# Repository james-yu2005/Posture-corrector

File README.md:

# 🎯 Posture Corrector Device

## 🎥 Demo Videos

Explore both iterations in action:

- ▶️ **ESP32 + OpenCV-based Posture Corrector (2nd Iteration)**  
- ▶️ **Arduino-based Posture Corrector (1st Iteration)**

📁 [Watch the Demo Videos on Google Drive](https://drive.google.com/drive/folders/1XhhxoisGqGbtTAvJfZo68UkWgdPwPm_9?usp=drive_link)

---

## 🧠 Overview

A wearable device that uses real-time sensor feedback and computer vision to promote proper posture.

This device monitors upper back and neck posture using an **MPU-6050** sensor and a custom **OpenCV** model. Upon detecting poor posture, it emits an audible alert via a buzzer to notify the user.

---

## 🔧 First Iteration (Prototype)

- Built using an **Arduino Uno R3**, **MPU-6050**, and a **breadboard**.
- Detected angular deviations in back posture and triggered a buzzer during slouching.

---

## 🚀 Second Iteration (Refined)

- Upgraded to an **ESP32** microcontroller for wireless communication and improved performance.
- Integrated an **OpenCV + MediaPipe** model to track **neck posture** using webcam input and calculate head tilt angles.
- Real-time communication between OpenCV and ESP32 triggers the buzzer when poor neck posture is detected.
- Designed a **3D-printed wearable enclosure** using **SolidWorks** to house the electronics.
- 📂 Computer vision source code: [OpenCV Posture Model](https://github.com/james-yu2005/posture_corrector_code)

---

## 🛠️ Hardware Improvements

- Designed a **custom PCB** to replace the breadboard, enhancing compactness, reliability, and ease of assembly.
- A new **SolidWorks 3D enclosure** is in development for the updated hardware version.

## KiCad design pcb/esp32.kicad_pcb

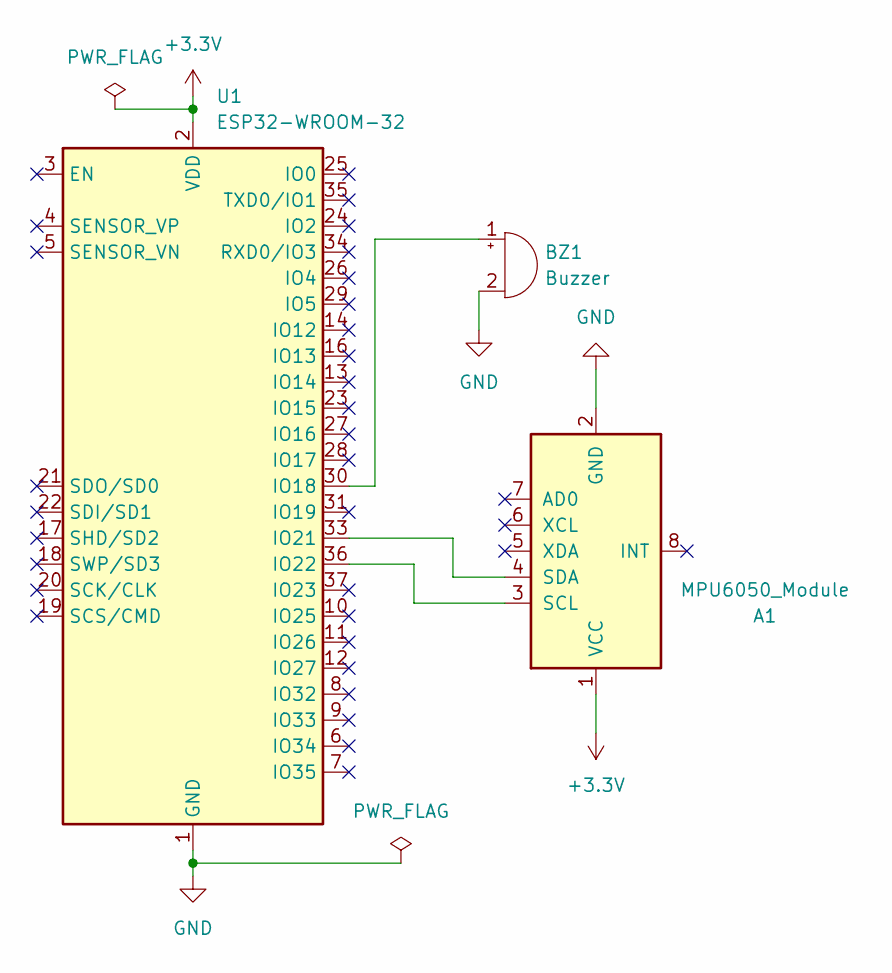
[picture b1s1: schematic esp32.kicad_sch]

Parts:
A1: MPU6050_Module
BZ1: Buzzer; Buzzer_12x9.5RM7.6
U1: ESP32-WROOM-32

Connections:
+3.3V: A1.1 (VCC), U1.2 (VDD)
GND: A1.2 (GND), BZ1.2 (-), U1.1 (GND), U1.15 (GND), U1.38 (GND), U1.39 (GND)
unnamed: A1.3 (SCL), U1.36 (IO22)
unnamed: A1.4 (SDA), U1.33 (IO21)
unnamed: BZ1.1 (+), U1.30 (IO18)

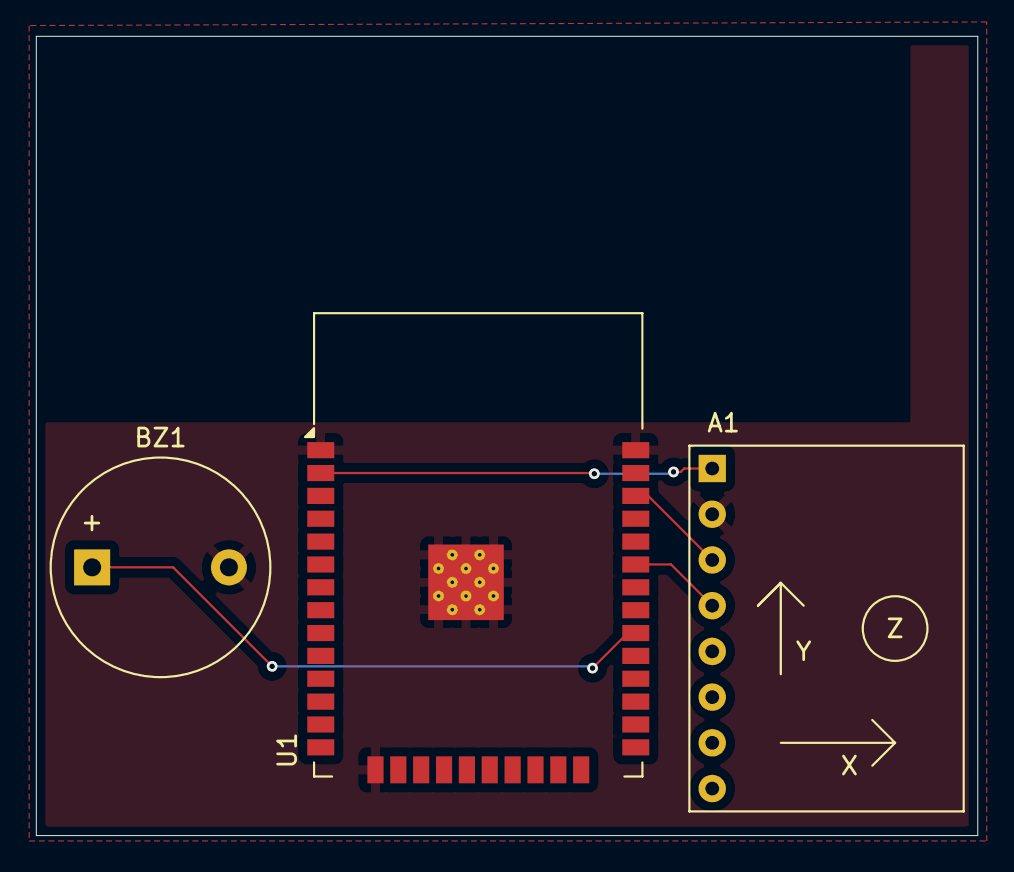
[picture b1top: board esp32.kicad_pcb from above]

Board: 4 copper layers, 52.3 x 44.4 mm, 3 parts (0 on the bottom side), 5 nets.

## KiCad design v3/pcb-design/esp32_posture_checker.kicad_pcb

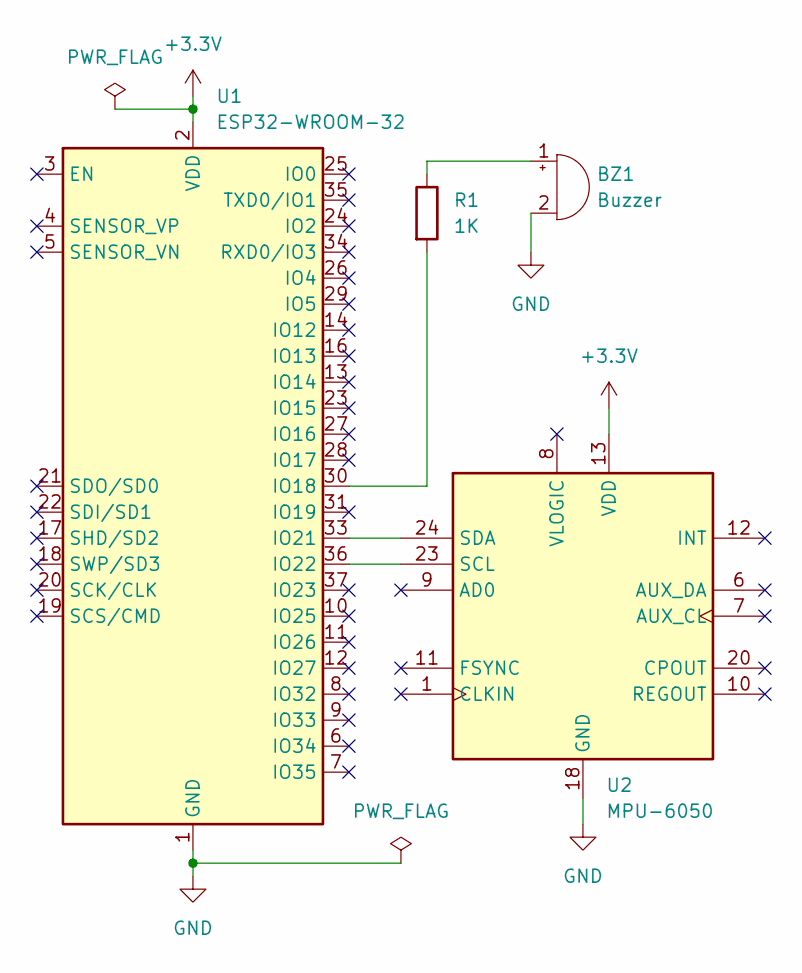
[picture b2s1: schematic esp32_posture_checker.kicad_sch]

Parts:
BZ1: Buzzer; Buzzer_12x9.5RM7.6
R1: 1K; R_Axial_DIN0207_L6.3mm_D2.5mm_P7.62mm_Horizontal
U1: ESP32-WROOM-32
U2: MPU-6050; InvenSense_QFN-24_4x4mm_P0.5mm

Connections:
+3.3V: U1.2 (VDD), U2.13 (VDD)
GND: BZ1.2 (-), U1.1 (GND), U1.15 (GND), U1.38 (GND), U1.39 (GND), U2.18 (GND)
unnamed: BZ1.1 (+), R1.1
unnamed: R1.2, U1.30 (IO18)
unnamed: U1.33 (IO21), U2.24 (SDA)
unnamed: U1.36 (IO22), U2.23 (SCL)

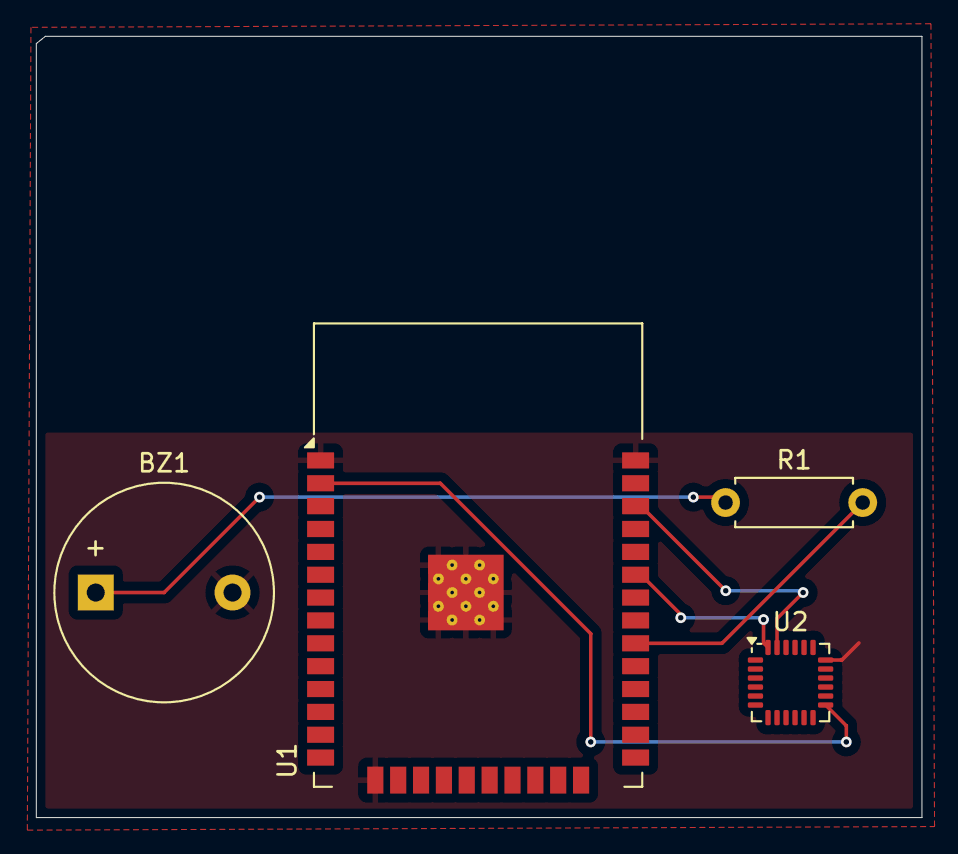
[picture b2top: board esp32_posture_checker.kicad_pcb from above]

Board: 4 copper layers, 49.2 x 43.4 mm, 4 parts (0 on the bottom side), 6 nets.

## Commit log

2025-02-25 Rename IMG_5406 (1).mov to posture_corrector_v1.mov
2025-03-04 Rename posture_corrector.ino to posture_corrector.cpp
2025-03-11 Rename posture_corrector.cpp to arduino_posture.cpp
2025-03-11 Create esp32_posture
2025-03-11 Rename esp32_posture to esp32_posture.cpp
2025-05-03 Create esp32_posture_monitor
2025-05-03 Update esp32_posture_monitor
2025-05-03 Create s
2025-05-03 Create pcb-design
2025-05-03 Create g
2025-05-03 Create example
2025-05-04 Rename posture.cpp to posture_corrector.cpp
2025-05-05 Rename posture_corrector_v1 (2).jpg to posture_corrector.jpg
2025-05-05 Rename IMG_5639.mov to posture_corrector.mov
